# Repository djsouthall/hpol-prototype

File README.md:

# RNO-G HPol Antenna Design

This design was finalized (for the current deployment cycle), and several dozen antennas have been built with this design.  Images of the finalized design can be seen below.  The antennas consist of 8in OD aluminum tubes with custom machining for slots and structural support holes.  The center feed consists of a custom set of connected PCB circuits, supported with several waterjet nylon inserts.  Each end of the antennas has waterjet cut nylon caps, with the top having additional structure to hold the front-end electronics.  These endcaps have rope strung through which is ultimately used to hang the antenna in the bore-hole.  

# Images
Opaque Element             |  Transparent Element
:-------------------------:|:-------------------------:
  |  

Feed
:--------------------------------------------------:
|  |

# Development Notes
This contains code, data, and design files created while working towards a finalized hpol antenna for RNO-G.

I use some functions that are defined from another package: [plot_ff.py](https://github.com/djsouthall/beacon/blob/master/tools/plot_ff.py).  These aren't complicated and could easily be redifined in this project, but I am the only one using it and this is fine for me. 

To use certain tools and scripts in this repository you may need to define the environment variables *BEACON_ANALYSIS_DIR* (as specified in the BEACON analysis code framework [BEACON](https://github.com/djsouthall/beacon)), as well as *HPOL_ANALYSIS_DIR*, which is similar but pointing to the folder containing this repository on your local machine. 

Additionally I am moving towards using direct imports of packages, which will require you to add these paths to your python path.

For example in my bashrc I have:
HPOL_ANALYSIS_DIR="/home/dsouthall/Projects/Greenland/hpol_prototype/"
export HPOL_ANALYSIS_DIR
export PYTHONPATH=$PYTHONPATH:/home/dsouthall/Projects/Greenland/

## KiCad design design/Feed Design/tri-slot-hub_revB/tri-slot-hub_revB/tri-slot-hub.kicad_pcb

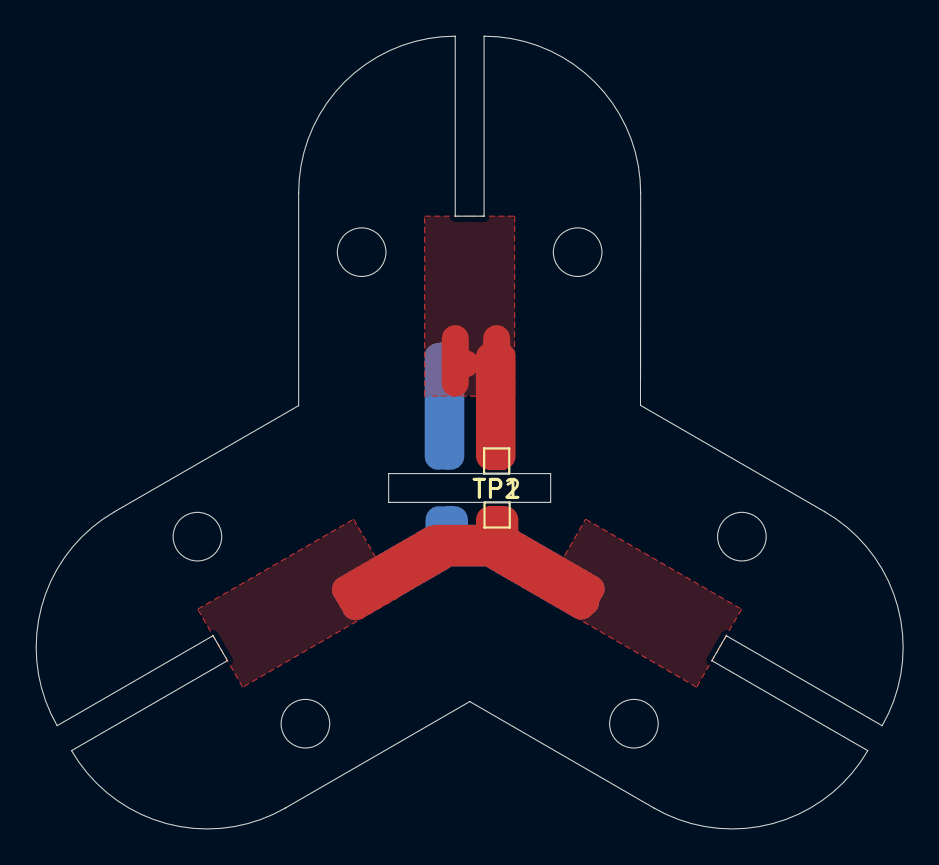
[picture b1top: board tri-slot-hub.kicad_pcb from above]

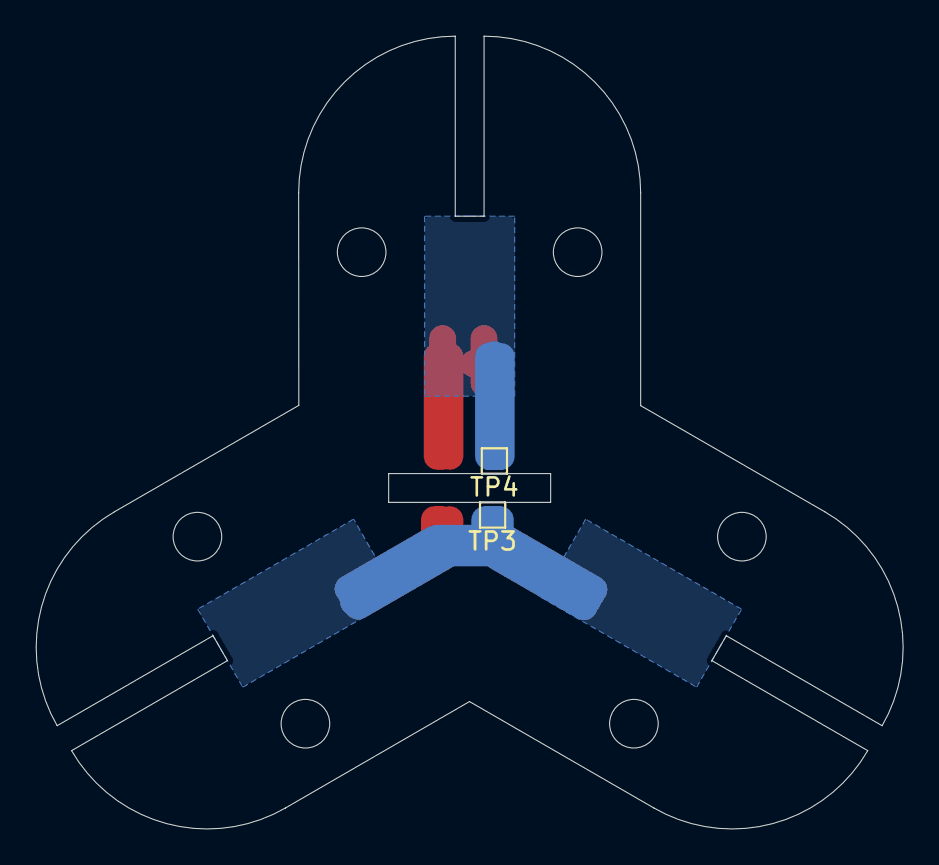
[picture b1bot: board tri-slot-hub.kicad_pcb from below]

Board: 2 copper layers, 48.2 x 44.0 mm, 4 parts (2 on the bottom side), 2 nets.

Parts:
TP1, TP2, TP3, TP4: TestPoint; TestPoint_Pad_1.0x1.0mm

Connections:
/slot_l: TP1.1, TP2.1
/slot_r: TP3.1, TP4.1

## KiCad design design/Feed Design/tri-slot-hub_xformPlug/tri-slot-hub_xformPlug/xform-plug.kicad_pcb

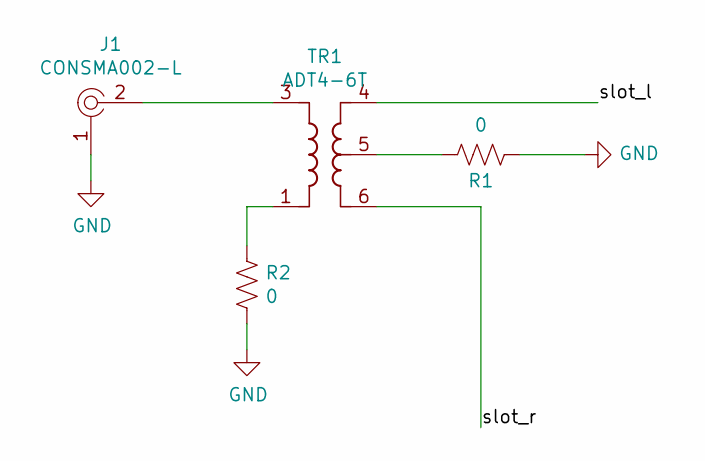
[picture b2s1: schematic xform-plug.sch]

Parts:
J1: CONSMA002-L; RF_SMA_RightAngle; Part Number CONSMA003-L
R1, R2: 0; 0603_R
TR1: ADT4-6T; Mini-Circuits_CD637_H5.23mm

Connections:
/slot_l: TR1.4
/slot_r: TR1.6
GND: J1.1, R1.1, R2.2
unnamed: J1.2, TR1.3
unnamed: R1.2, TR1.5
unnamed: R2.1, TR1.1

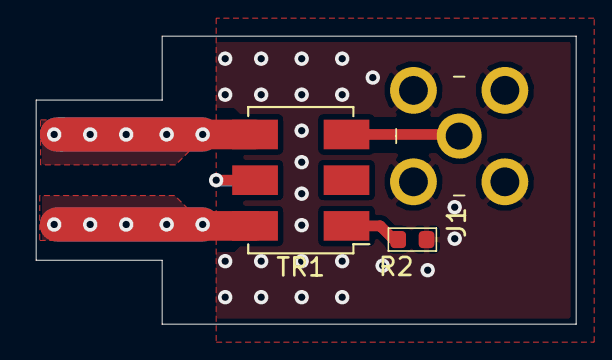
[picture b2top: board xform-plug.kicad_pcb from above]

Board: 2 copper layers, 30.0 x 16.0 mm, 4 parts (1 on the bottom side), 4 nets.

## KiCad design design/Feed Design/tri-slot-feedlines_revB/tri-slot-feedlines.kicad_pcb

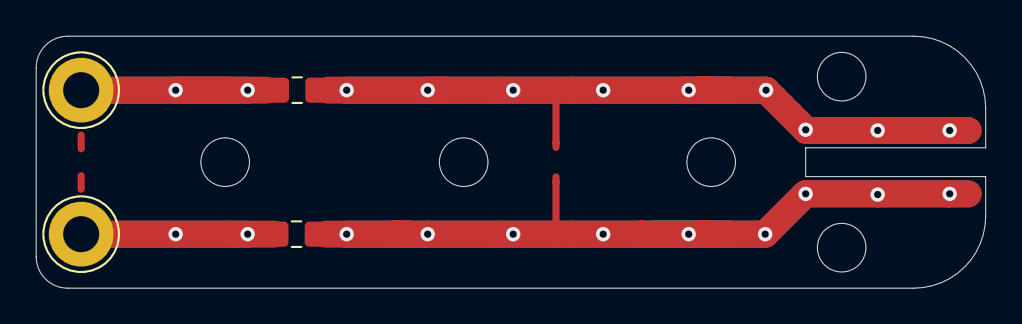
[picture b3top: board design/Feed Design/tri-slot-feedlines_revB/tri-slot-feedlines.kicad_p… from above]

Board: 2 copper layers, 52.8 x 14.0 mm, 4 parts (0 on the bottom side), 2 nets.

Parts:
C1, C2: C; C_0805_2012Metric_Pad1.15x1.40mm_HandSolder
slot_l1: TestPoint; TestPoint_Loop_D3.80mm_Drill2.0mm
slot_r1: TestPoint; TestPoint_Loop_D3.80mm_Drill2.0mm

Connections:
unnamed: C1.2, slot_l1.1
unnamed: C2.2, slot_r1.1

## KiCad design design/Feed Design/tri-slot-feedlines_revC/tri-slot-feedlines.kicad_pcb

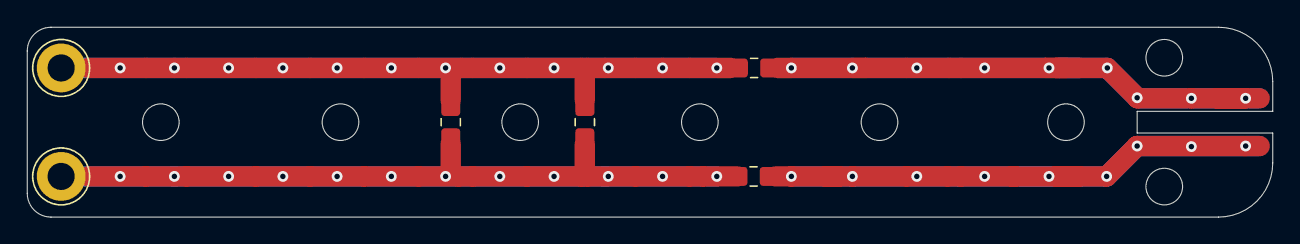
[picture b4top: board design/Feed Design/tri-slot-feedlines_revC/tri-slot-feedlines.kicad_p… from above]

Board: 2 copper layers, 91.8 x 14.0 mm, 6 parts (0 on the bottom side), 2 nets.

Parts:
C1, C2, C3, C4: C; C_0805_2012Metric_Pad1.15x1.40mm_HandSolder
slot_l1: TestPoint; TestPoint_Loop_D3.80mm_Drill2.0mm
slot_r1: TestPoint; TestPoint_Loop_D3.80mm_Drill2.0mm

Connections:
unnamed: C1.2, C3.2, C4.1, slot_l1.1
unnamed: C2.2, C3.1, C4.2, slot_r1.1

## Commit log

2020-03-02 Adding everything.
2020-03-02 Updated some description of the code to make it clear this is not my best work.
2020-05-26 Added the files used for S21 measurements a long time ago.
2020-08-20 Added some code to help predict the effects of adding inductors to the centerfeed. I would like to also use this tool to determine why what we measure is not what we predict.
2020-08-21 Added some better organization for importing.
2020-08-21 Added another script. Investigating behaviour of adding L. Should not trust code at current stage.
2020-08-21 Fixed the bug which was causing difference when adding multiple parts.
2020-09-24 Updated the shunt investigation script from recent work. Additionally the SmithMatcher class has been given much of the functionality of the daughter HpolTriWing class and should be used.
2020-09-28 Added 22nh Al measurements.
2020-09-29 Making plots for presentation.
2020-09-30 Made some plots for the presentation and uploaded more data.
2020-10-01 Added more data.
2020-10-09 Added design files to this repository.
    Added both the inventor models and the current kicad files for the HPol prototype. I have been working on these for a while but they were not on git.
2020-10-09 Create digikey-mockup-A114140-ND_8in.stp
    Added the current mockup for a bent A114140-ND part to fit within the 8in antenna.
2020-10-09 Updated models of insert and can for 2 support holes and added tolerance.
2020-10-09 Added Cu traces to feedline model for 8in.
2020-10-16 Added hub parts from Eric
2020-10-18 Added plot file.
2020-10-19 Pushing Cam files
2020-10-19 Laying groundwork for quadslot build.
2020-10-19 Quad slot parts underway
    The quadslot open and closed versions are moving long. Closed is complete likely to an orderable state, the open needs more work to account for holes and structural supports.
2020-10-19 Fixing some things with the trislots. Adding open trislots.
    Minor changes to fix constraints found when making quadslot.
2020-10-20 Good progress on quad hub design. Just need to check for hardware conflicts.
2020-10-20 Added some work towards testing the presence of a transformer. It is all very incomplete.
2020-10-27 Updating trislots and other parts.
2020-11-03 Pushing updated data and model stp files.
2020-11-04 Updated model
2020-11-07 data
    data
2020-11-12 Adding data
2020-11-13 Cad and drawing files updated.
2020-11-13 Further update on drawings
2020-11-19 A lot of model changes in prep for RNO-G report. Made end caps.
2020-11-19 Slight changes to design files. Included the front end box.
2020-11-19 Added some wiggle room to inserts
2020-12-08 Updates for making the end cap drawing.
    Updates for making the end cap drawing.
2021-07-13 Adding images from Inventor of the finalized HPol design.
2023-01-09 fixed some typos in README
